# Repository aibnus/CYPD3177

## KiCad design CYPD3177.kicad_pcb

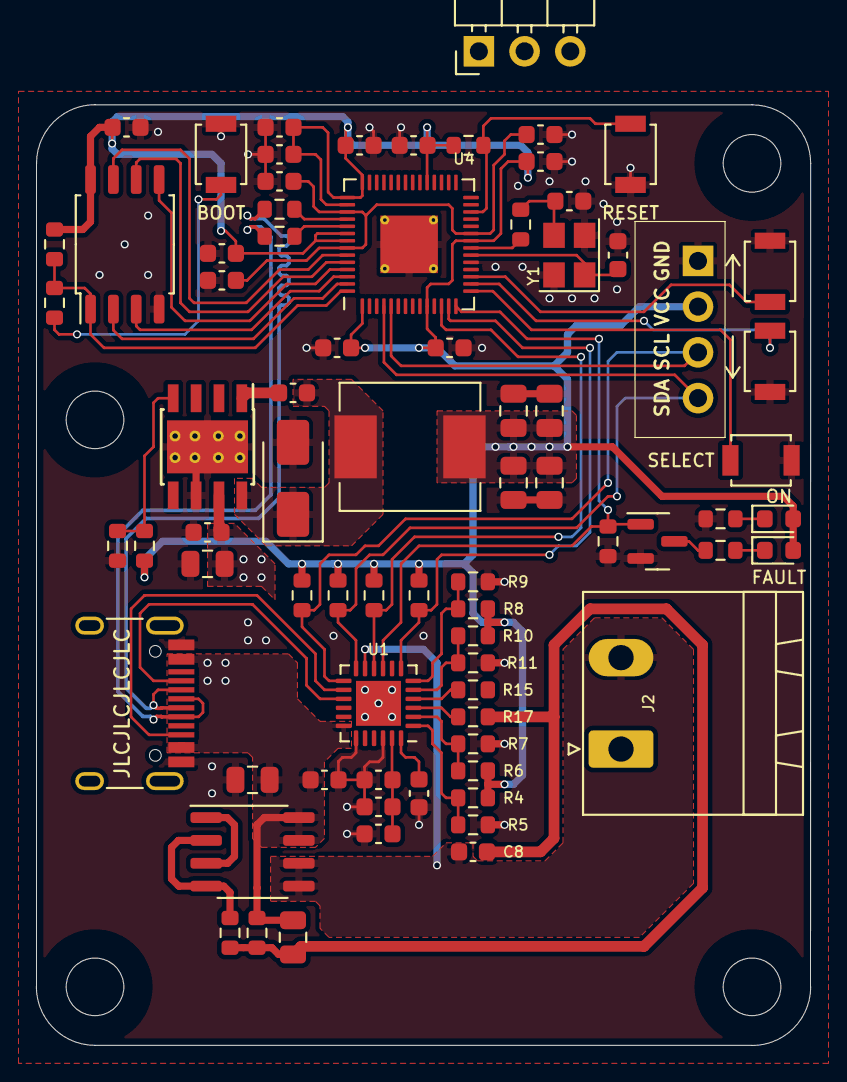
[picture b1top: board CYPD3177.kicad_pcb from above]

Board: 2 copper layers, 43.0 x 52.3 mm, 76 parts (0 on the bottom side), 49 nets.

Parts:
C1, C2: 1u; C_0603_1608Metric
C3, C4, C6, C8, C12, C16, C17, C20, C21, C22, C23, C24, C25, C26, C28: 100n; C_0603_1608Metric
C5, C7, C10, C11, C13, C14, C15: 47u; C_0805_2012Metric
C9: 10n; C_0603_1608Metric
C18, C19: 2u2; C_0603_1608Metric
C29, C30: 20pF; C_0603_1608Metric
D1: red; LED_0603_1608Metric
D2: B340A; D_SMA
D3: green; LED_0603_1608Metric
J1: USB_C_Receptacle_USB2.0; USB_C_Receptacle_HRO_TYPE-C-31-M-12
J2: Conn_01x02; PhoenixContact_MSTBA_2,5_2-G-5,08_1x02_P5.08mm_Horizontal
J4: Conn_01x04; SSD1306-0.91-OLED-4pin-128x32
J5: Conn_01x03; PinHeader_1x03_P2.54mm_Horizontal
L1: 15u; L_Chilisin_BMRB00060650
Q1: AO3400A; SOT-23
Q2: DMP3098LSD; SO-8_3.9x4.9mm_P1.27mm
R1, R19: 10k; R_0603_1608Metric
R2, R4, R8, R21: 1k2; R_0603_1608Metric
R3, R12, R13, R14, R15, R16, R17, R18: 2k2; R_0603_1608Metric
R5, R6, R7, R9, R10, R11: 5k1; R_0603_1608Metric
R20: 5k6; R_0603_1608Metric
R22, R23: 27; R_0603_1608Metric
R29, R34: 1k; R_0603_1608Metric
R31, R33: 47k; R_0603_1608Metric
SW1, SW2, SW3: SW_Push; SW_SPST_B3U-1000P
SW_BOOT1: SW_Push; SW_SPST_B3U-1000P
SW_RESET1: SW_Push; SW_SPST_B3U-1000P
U1: CYPD3177; VQFN-24-1EP_4x4mm_P0.5mm_EP2.5x2.5mm
U2: TPS5430DDA; TI_SO-PowerPAD-8_ThermalVias
U4: RP2040; QFN-56-1EP_7x7mm_P0.4mm_EP3.2x3.2mm_ThermalVias
U5: W25Q128JVS; SOIC-8_5.23x5.23mm_P1.27mm
Y1: 12MHz; Crystal_SMD_3225-4Pin_3.2x2.5mm

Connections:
+1V1: C16.2, C17.2, C18.2, U4.23 (DVDD), U4.45 (VREG_VOUT), U4.50 (DVDD)
+1V8: C1.1, U1.24 (VCCD)
+3.3V: C2.1, C3.1, C4.1, U1.23 (VDDD)
+3V3: C10.1, C13.1, C14.1, C15.1, C19.1, C20.1, C21.1, C22.1, C23.1, C24.1, C25.1, C26.1, C28.1, D1.2 (A), D3.2 (A), J4.2, L1.2, R3.1, R4.1, R6.1, R8.1, R10.1, R12.1, R13.1, R14.1, R19.1, R31.1, R33.1, U4.1 (IOVDD), U4.10 (IOVDD), U4.22 (IOVDD), U4.33 (IOVDD), U4.42 (IOVDD), U4.43 (ADC_AVDD), U4.44 (VREG_IN), U4.48 (USB_VDD), U4.49 (IOVDD), U5.8 (VCC)
/D_N: J1.A7 (D-), J1.B7 (D-), R23.2
/D_P: J1.A6 (D+), J1.B6 (D+), R22.2
/FAULT: Q1.1 (G), R1.1, U1.9 (FAULT), U4.14 (GPIO11)
/FLIP: R3.2, U1.10 (FLIP), U4.12 (GPIO9)
/INT: R12.2, U1.7 (HPI_INT), U4.13 (GPIO10)
/MCU/BOOT: R34.1, SW_BOOT1.2
/MCU/GPIO12: SW3.1, U4.15 (GPIO12)
/MCU/GPIO13: SW2.1, U4.16 (GPIO13)
/MCU/GPIO14: SW1.1, U4.17 (GPIO14)
/MCU/NRST: R31.2, SW_RESET1.2, U4.26 (RUN)
/MCU/QSPI_SCLK: U4.52 (QSPI_SCLK), U5.6 (CLK)
/MCU/QSPI_SD0: U4.53 (QSPI_SD0), U5.5 (DI(IO0))
/MCU/QSPI_SD1: U4.55 (QSPI_SD1), U5.2 (DO(IO1))
/MCU/QSPI_SD2: U4.54 (QSPI_SD2), U5.3 (IO2)
/MCU/QSPI_SD3: U4.51 (QSPI_SD3), U5.7 (IO3)
/MCU/QSPI_SS: R33.2, R34.2, U4.56 (QSPI_SS), U5.1 (~CS)
/MCU/SWCLK: J5.3, U4.24 (SWCLK)
/MCU/SWDIO: J5.2, U4.25 (SWD)
/SCL: J4.3, R14.2, U1.13 (HPI_SCL), U4.5 (GPIO3)
/SDA: J4.4, R13.2, U1.12 (HPI_SDA), U4.4 (GPIO2)
GND: C1.2, C2.2, C3.2, C4.2, C5.2, C6.2, C10.2, C11.2, C12.2, C13.2, C14.2, C15.2, C16.1, C17.1, C18.1, C19.2, C20.2, C21.2, C22.2, C23.2, C24.2, C25.2, C26.2, C28.2, C29.1, C30.2, D2.2 (A), J1.A1 (GND), J1.A12 (GND), J1.B1 (GND), J1.B12 (GND), J2.1, J4.1, J5.1, Q1.2 (S), R1.2, R5.2, R7.2, R9.2, R11.2, R20.2, R21.2, SW1.2, SW2.2, SW3.2, SW_BOOT1.1, SW_RESET1.1, U1.19 (GND), U1.22 (VSS), U1.25 (EPAD), U2.6 (GND), U2.9 (GNDPAD), U4.19 (TESTEN), U4.57 (GND), U5.4 (GND), Y1.2, Y1.4
unnamed: C7.2, C8.2, R16.2, R17.1, R18.2
unnamed: C30.1, R29.1, Y1.3
unnamed: D1.1 (K), R2.1
unnamed: C9.2, D2.1 (K), L1.1, U2.8 (PH)
unnamed: D3.1 (K), R21.1
unnamed: J1.A5 (CC1), U1.15 (CC1)
unnamed: J1.B5 (CC2), U1.14 (CC2)
unnamed: C8.1, J2.2, Q2.5 (D), Q2.6 (G), U1.11 (VDC_OUT)
unnamed: Q1.3 (D), R2.2
unnamed: Q2.2 (G), Q2.4 (G), R16.1
unnamed: Q2.1 (S), Q2.3 (S)
unnamed: R10.2, R11.1, U1.5 (ISNK_COARSE)
unnamed: R8.2, R9.1, U1.6 (ISNK_FINE)
unnamed: R15.1, U1.4 (SAFE_PWR_EN)
unnamed: R17.2, U1.3 (VBUS_FET_EN)
unnamed: R6.2, R7.1, U1.2 (VBUS_MAX)
unnamed: R4.2, R5.1, U1.1 (VBUS_MIN)
unnamed: C9.1, U2.1 (BOOT)
unnamed: R19.2, R20.1, U2.4 (VSENSE)
unnamed: R23.1, U4.46 (USB_DM)
unnamed: R22.1, U4.47 (USB_DP)
unnamed: C29.2, U4.20 (XIN), Y1.1
unnamed: R29.2, U4.21 (XOUT)
VBUS: C5.1, C6.1, C7.1, C11.1, C12.1, J1.A4 (VBUS), J1.A9 (VBUS), J1.B4 (VBUS), J1.B9 (VBUS), Q2.7 (D), Q2.8 (G), R18.1, U1.18 (VBUS_IN), U2.7 (VIN)

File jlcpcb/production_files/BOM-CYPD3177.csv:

Comment,Designator,Footprint,LCSC
27,R23,R_0603_1608Metric,
47u,C15,C_0805_2012Metric,
10k,R1,R_0603_1608Metric,
100n,C3,C_0603_1608Metric,
100n,C20,C_0603_1608Metric,
100n,C28,C_0603_1608Metric,
5k1,R5,R_0603_1608Metric,
47u,C5,C_0805_2012Metric,
100n,C8,C_0603_1608Metric,
SW_Push,SW_RESET1,SW_SPST_B3U-1000P,
20pF,C29,C_0603_1608Metric,
Conn_01x03,J5,PinHeader_1x03_P2.54mm_Horizontal,
100n,C26,C_0603_1608Metric,
AO3400A,Q1,SOT-23,
100n,C4,C_0603_1608Metric,
100n,C25,C_0603_1608Metric,
Conn_01x02,J2,"PhoenixContact_MSTBA_2,5_2-G-5,08_1x02_P5.08mm_Horizontal",
27,R22,R_0603_1608Metric,
100n,C6,C_0603_1608Metric,
12MHz,Y1,Crystal_SMD_3225-4Pin_3.2x2.5mm,
2u2,C19,C_0603_1608Metric,
5k1,R9,R_0603_1608Metric,
SW_Push,SW2,SW_SPST_B3U-1000P,
2k2,R14,R_0603_1608Metric,
1k,R34,R_0603_1608Metric,
2k2,R3,R_0603_1608Metric,
2k2,R16,R_0603_1608Metric,
2k2,R12,R_0603_1608Metric,
TPS5430DDA,U2,TI_SO-PowerPAD-8_ThermalVias,
47u,C11,C_0805_2012Metric,
1k2,R2,R_0603_1608Metric,
DMP3098LSD,Q2,SO-8_3.9x4.9mm_P1.27mm,
5k1,R6,R_0603_1608Metric,
2k2,R15,R_0603_1608Metric,
10k,R19,R_0603_1608Metric,
green,D3,LED_0603_1608Metric,
47k,R31,R_0603_1608Metric,
1u,C2,C_0603_1608Metric,
SW_Push,SW3,SW_SPST_B3U-1000P,
100n,C17,C_0603_1608Metric,
5k1,R10,R_0603_1608Metric,
100n,C23,C_0603_1608Metric,
1u,C1,C_0603_1608Metric,
SW_Push,SW1,SW_SPST_B3U-1000P,
47u,C14,C_0805_2012Metric,
5k1,R7,R_0603_1608Metric,
2k2,R13,R_0603_1608Metric,
2k2,R18,R_0603_1608Metric,
2u2,C18,C_0603_1608Metric,
B340A,D2,D_SMA,
USB_C_Receptacle_USB2.0,J1,USB_C_Receptacle_HRO_TYPE-C-31-M-12,
20pF,C30,C_0603_1608Metric,
1k,R29,R_0603_1608Metric,
100n,C16,C_0603_1608Metric,
15u,L1,L_Chilisin_BMRB00060650,
SW_Push,SW_BOOT1,SW_SPST_B3U-1000P,
47u,C13,C_0805_2012Metric,
47u,C10,C_0805_2012Metric,
10n,C9,C_0603_1608Metric,
1k2,R21,R_0603_1608Metric,
2k2,R17,R_0603_1608Metric,
W25Q128JVS,U5,SOIC-8_5.23x5.23mm_P1.27mm,
5k6,R20,R_0603_1608Metric,
100n,C22,C_0603_1608Metric,
100n,C21,C_0603_1608Metric,
47u,C7,C_0805_2012Metric,
CYPD3177,U1,VQFN-24-1EP_4x4mm_P0.5mm_EP2.5x2.5mm,
red,D1,LED_0603_1608Metric,
100n,C24,C_0603_1608Metric,
RP2040,U4,QFN-56-1EP_7x7mm_P0.4mm_EP3.2x3.2mm_ThermalVias,
5k1,R11,R_0603_1608Metric,
100n,C12,C_0603_1608Metric,
Conn_01x04,J4,SSD1306-0.91-OLED-4pin-128x32,
